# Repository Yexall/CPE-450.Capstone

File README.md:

# CPE-450.Capstone
Authors:
- Cameron Bracken
- Ryan Jacoby
- Noa Johnson
- Yexelle Nash Segovia

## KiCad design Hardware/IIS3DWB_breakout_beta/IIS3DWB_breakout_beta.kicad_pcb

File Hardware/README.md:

# Haas Hooligans Hardware

Board assembly prints and schematics for the final prototypes are provided in this directory. The three folders (IIS3DWB\_eval, IIS3DWB\_breakout\_beta, and hw\_alpha) have more detailed design sources for each of the PCBs designed.

## Main Board
Bringup notes and notes for the next revision of the main board can be found [here](https://github.com/Yexall/CPE-450.Capstone/blob/main/Hardware/hw_alpha/bringup_notes.md)

An interactive HTML BOM can be found [here](https://html-preview.github.io/?url=https://github.com/Yexall/CPE-450.Capstone/blob/main/Hardware/hw_alpha/bom/ibom.html)

A downloadable PDF assembly document can be found [here](https://github.com/Yexall/CPE-450.Capstone/blob/main/Hardware/hw_alpha/plots/hw_alpha__Assembly.pdf)

A downloadable PDF schematic can be found [here](https://github.com/Yexall/CPE-450.Capstone/blob/main/Hardware/hw_alpha/hw_alpha_schem.pdf)

## IIS3DWB Breakout
A downloadable PDF assembly document can be found [here](https://github.com/Yexall/CPE-450.Capstone/blob/main/Hardware/IIS3DWB_breakout_beta/plots/IIS3DWB_breakout_beta__Assembly.pdf)

A downloadable PDF schematic can be found [here](https://github.com/Yexall/CPE-450.Capstone/blob/main/Hardware/IIS3DWB_breakout_beta/IIS3DWB_breakout_beta_schem.pdf)

## Copyright
Copyright Ryan Jacoby, Cal Poly CPE Department, Cal Poly IME Department 2025.

This source describes Open Hardware and is licensed under the CERN-OHL-P v2

You may redistribute and modify this documentation and make products
using it under the terms of the CERN-OHL-P v2 (https:/cern.ch/cern-ohl).
This documentation is distributed WITHOUT ANY EXPRESS OR IMPLIED
WARRANTY, INCLUDING OF MERCHANTABILITY, SATISFACTORY QUALITY
AND FITNESS FOR A PARTICULAR PURPOSE. Please see the CERN-OHL-P v2
for applicable conditions

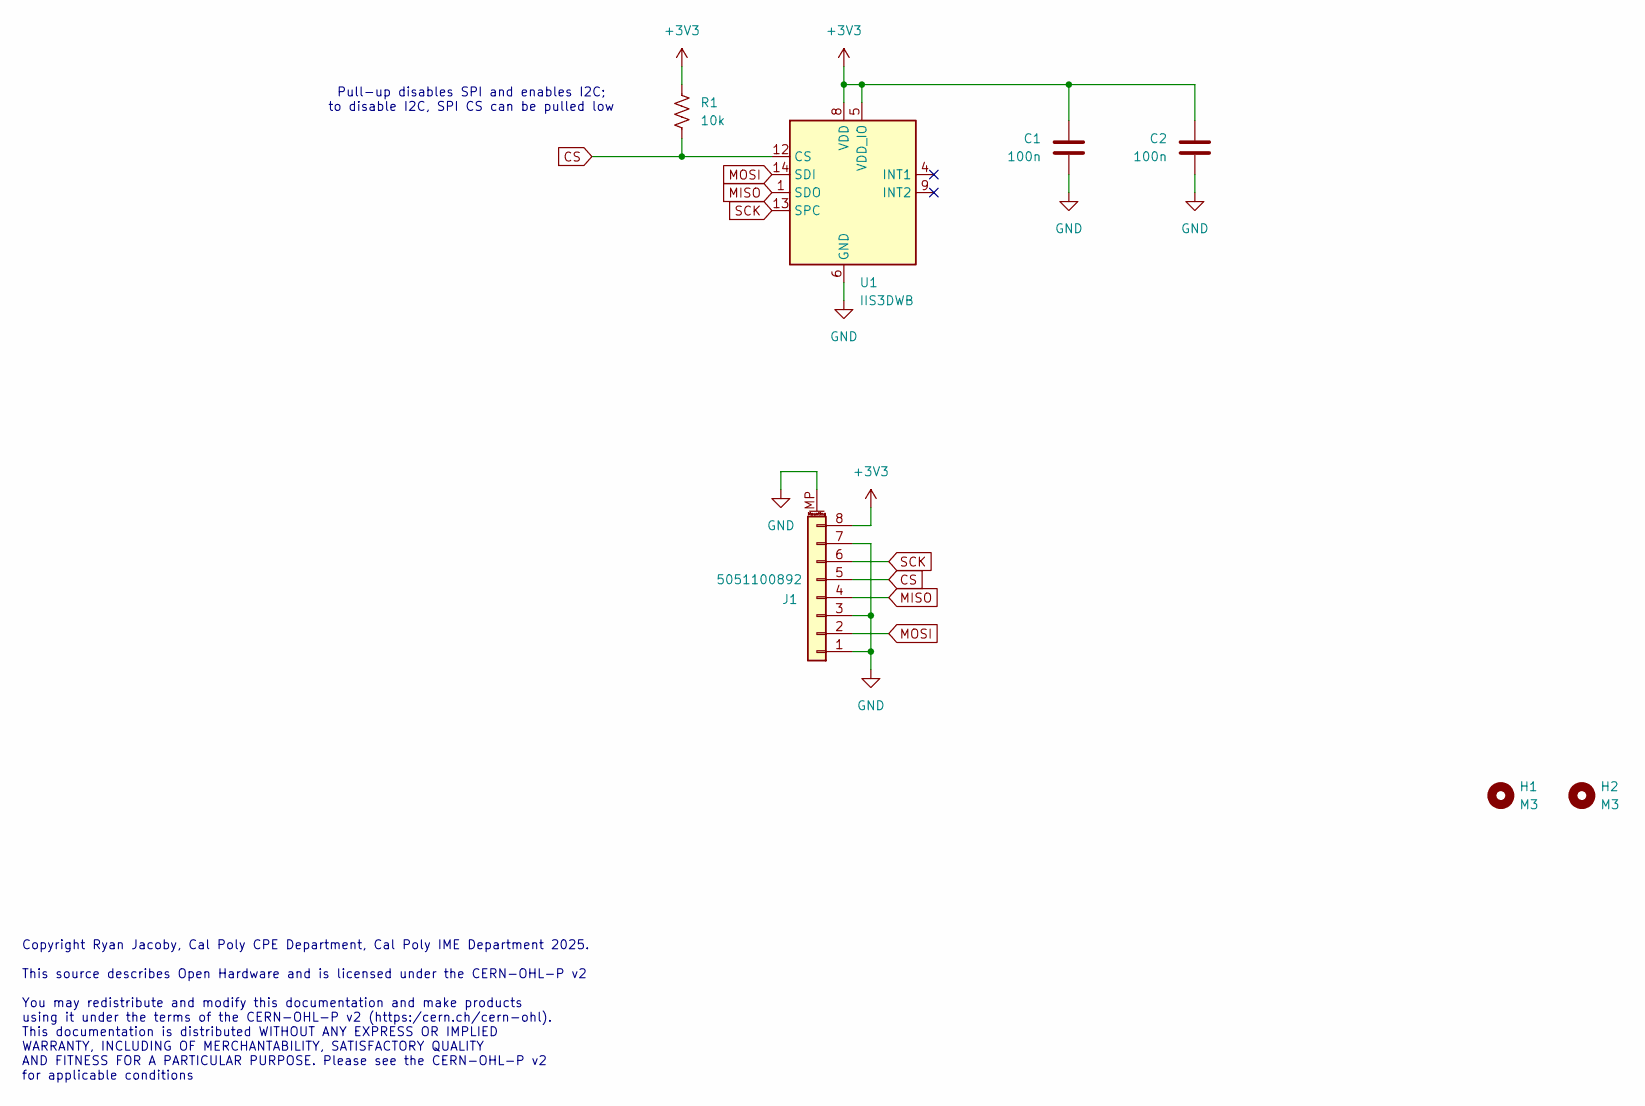
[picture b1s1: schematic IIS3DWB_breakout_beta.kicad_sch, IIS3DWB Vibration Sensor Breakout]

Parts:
C1, C2: 100n; C_0603_1608Metric
H1, H2: M3; MountingHole_3.2mm_M3
J1: 5051100892; CON_5051100892_MOL
R1: 10k; R_0603_1608Metric
U1: IIS3DWB; LGA-14_3x2.5mm_P0.5mm_LayoutBorder3x4y; MPN IIS3DWBTR

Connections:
+3V3: C1.1, C2.1, J1.8, R1.1, U1.5 (VDD_IO), U1.8 (VDD)
CS: J1.5, R1.2, U1.12 (CS)
GND: C1.2, C2.2, J1.1, J1.3, J1.7, J1.MP (MountPin), U1.2 (GND), U1.3 (GND), U1.6 (GND), U1.7 (GND)
MISO: J1.4, U1.1 (SDO)
MOSI: J1.2, U1.14 (SDI)
SCK: J1.6, U1.13 (SPC)

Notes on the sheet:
Copyright Ryan Jacoby, Cal Poly CPE Department, Cal Poly IME Department 2025. This source describes Open Hardware and is licensed under the CERN-OHL-P v2 You may redistribute and modify this documentation and make products using it under the terms of the CERN-OHL-P v2 (https:/cern.ch/cern-ohl). Thi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
Pull-up disables SPI and enables I2C; to disable I2C, SPI CS can be pulled low

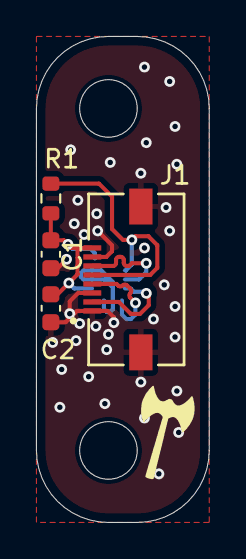
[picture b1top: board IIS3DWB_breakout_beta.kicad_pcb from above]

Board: 2 copper layers, 9.6 x 27.0 mm, 7 parts (1 on the bottom side), 6 nets.

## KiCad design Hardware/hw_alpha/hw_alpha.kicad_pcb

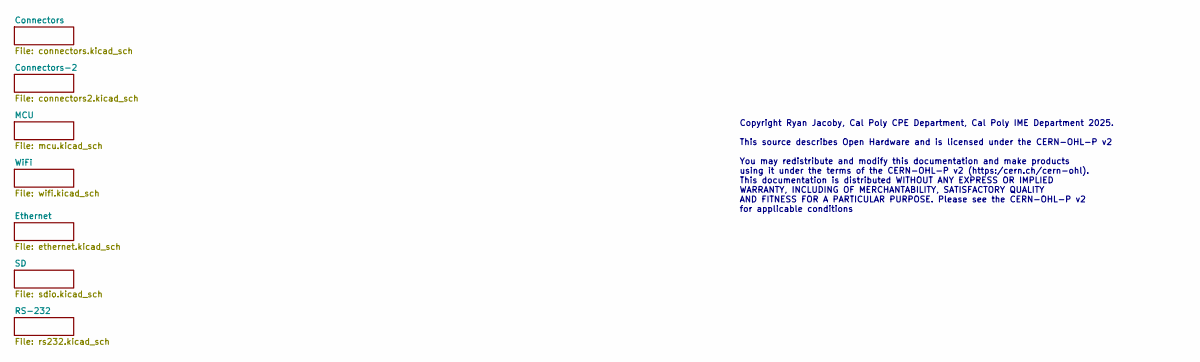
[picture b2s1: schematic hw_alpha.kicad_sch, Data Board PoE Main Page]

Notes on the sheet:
Copyright Ryan Jacoby, Cal Poly CPE Department, Cal Poly IME Department 2025. This source describes Open Hardware and is licensed under the CERN-OHL-P v2 You may redistribute and modify this documentation and make products using it under the terms of the CERN-OHL-P v2 (https:/cern.ch/cern-ohl). Thi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

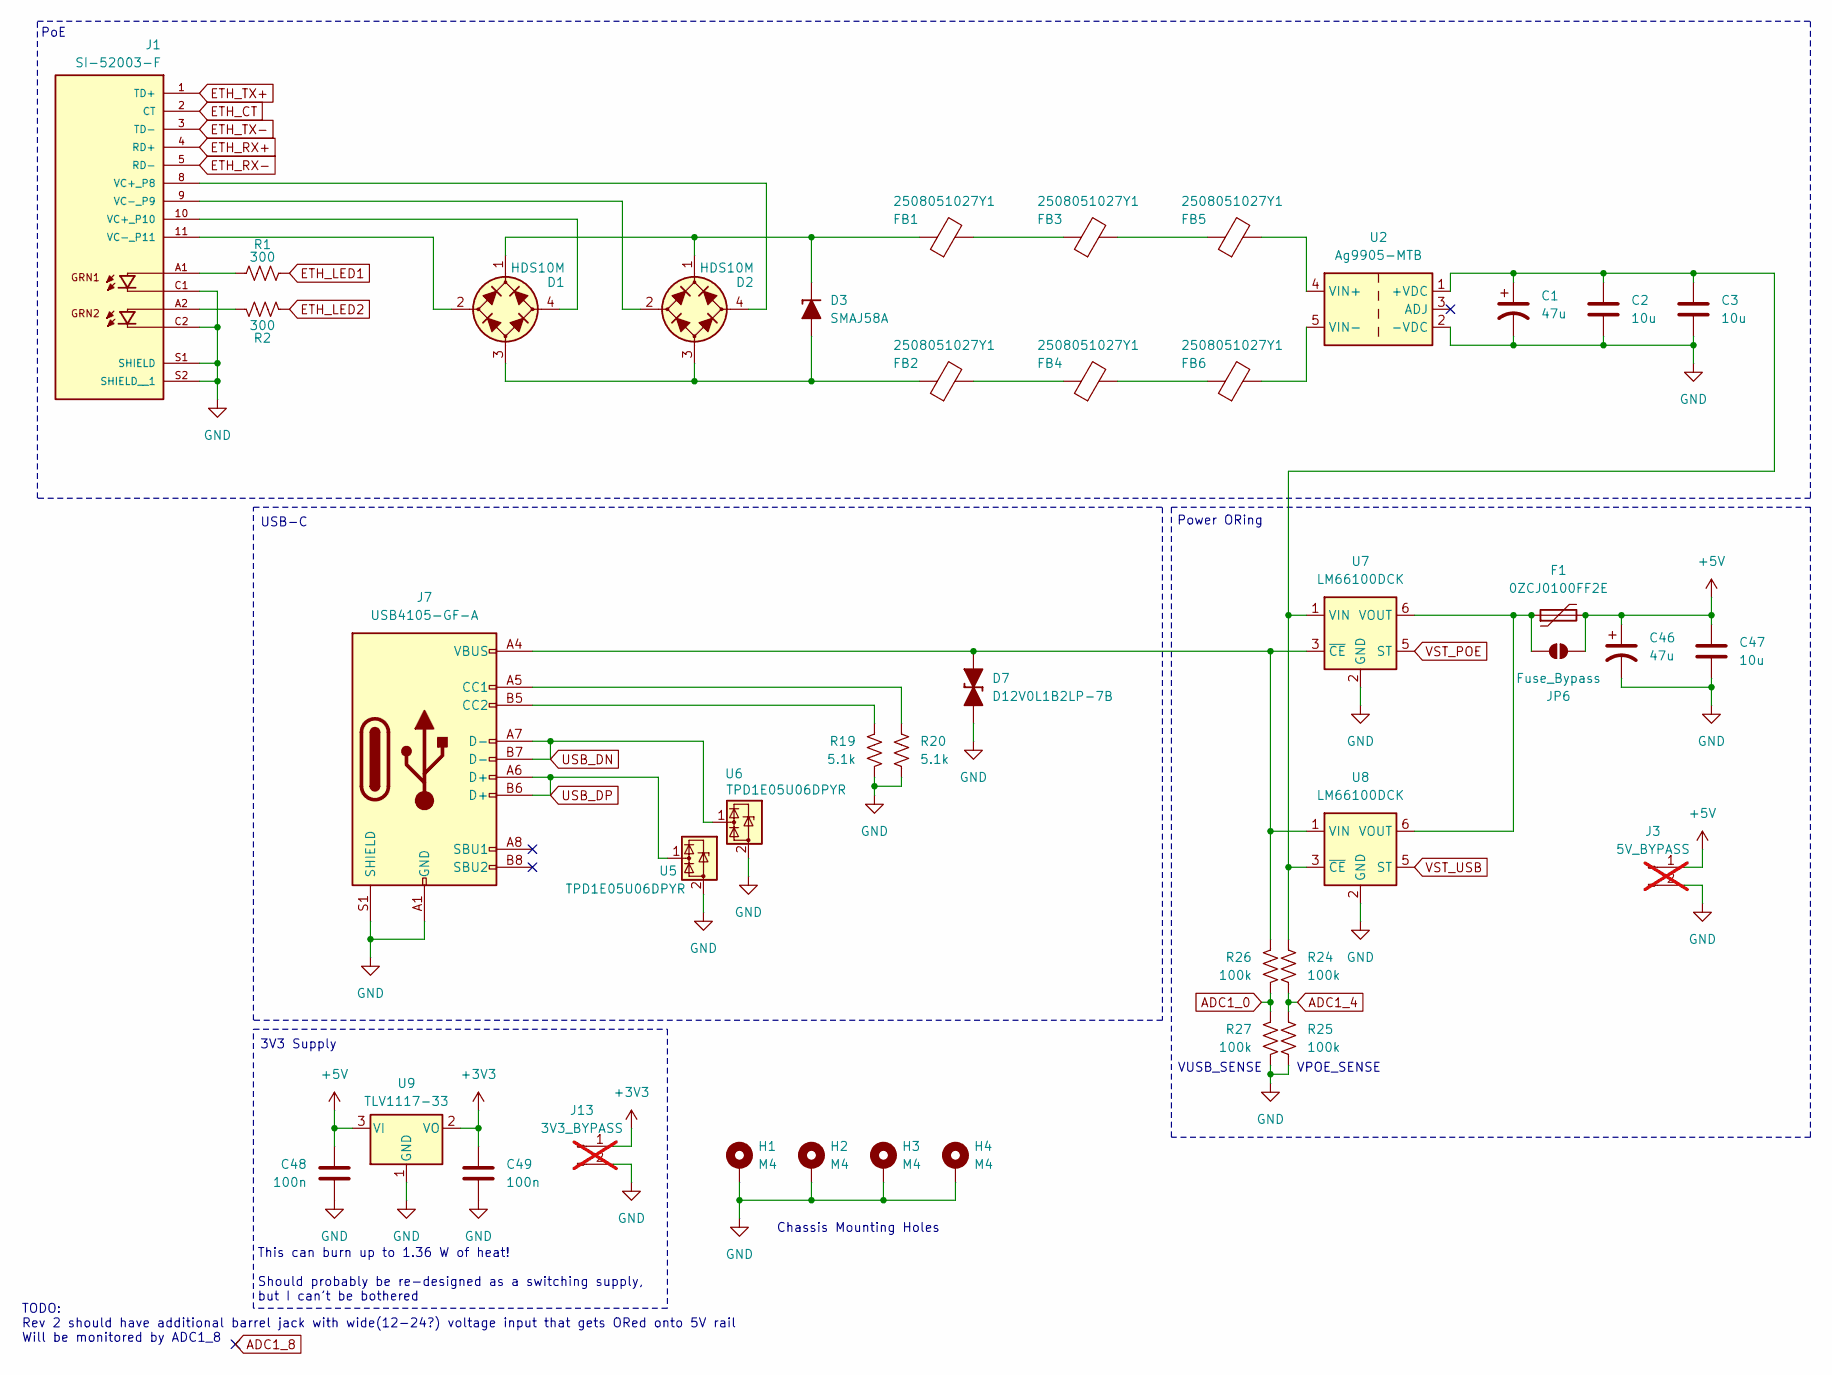
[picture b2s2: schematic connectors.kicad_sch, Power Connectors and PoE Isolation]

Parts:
C1, C46: 47u; CP_Elec_5x5.4
C2, C3, C47: 10u; C_0805_2012Metric
C48, C49: 100n; C_0603_1608Metric
D1, D2: HDS10M; HDS_DIO
D3: SMAJ58A; D_SMA
D7: D12V0L1B2LP-7B; D_0402_1005Metric
F1: 0ZCJ0100FF2E; Fuse_1206_3216Metric
FB1, FB2, FB3, FB4, FB5, FB6: 2508051027Y1; L_0805_2012Metric
H1, H2, H3, H4: M4; MountingHole_4.3mm_M4_Pad_Via
J1: SI-52003-F; BEL_SI-52003-F
J3: 5V_BYPASS; PinSocket_1x02_P2.54mm_Vertical; not fitted
J7: USB4105-GF-A; GCT_USB4105-GF-A
J13: 3V3_BYPASS; PinSocket_1x02_P2.54mm_Vertical; not fitted
JP6: Fuse_Bypass; SolderJumper-2_P1.3mm_Open_TrianglePad1.0x1.5mm
R1, R2: 300; R_0603_1608Metric
R19, R20: 5.1k; R_0603_1608Metric
R24, R25, R26, R27: 100k; R_0603_1608Metric
U2: Ag9905-MTB; Converter_DCDC_Silvertel_AG99xxMTB_Hand_Solder
U5, U6: TPD1E05U06DPYR; Texas_DPY0002A_0.6x1mm_P0.65mm
U7, U8: LM66100DCK; SOT-363_SC-70-6
U9: TLV1117-33; SOT-223-3_TabPin2

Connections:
+3V3: C49.1, J13.1, U9.2 (VO); also elsewhere on the board
+5V: C46.1, C47.1, C48.1, F1.2, J3.1, JP6.2 (B), U9.3 (VI); also elsewhere on the board
ADC1_0: R26.2, R27.1; also elsewhere on the board
ADC1_4: R24.2, R25.1; also elsewhere on the board
ETH_CT: J1.2 (CT); also elsewhere on the board
ETH_LED1: R1.2; also elsewhere on the board
ETH_LED2: R2.2; also elsewhere on the board
ETH_RX+: J1.4 (RD+); also elsewhere on the board
ETH_RX-: J1.5 (RD-); also elsewhere on the board
ETH_TX+: J1.1 (TD+); also elsewhere on the board
ETH_TX-: J1.3 (TD-); also elsewhere on the board
GND: C1.2, C2.2, C3.2, C46.2, C47.2, C48.2, C49.2, D7.1 (K), H1.1, H2.1, H3.1, H4.1, J1.C1, J1.C2, J1.S1 (SHIELD), J1.S2 (SHIELD__1), J3.2, J7.A1 (GND), J7.A12 (GND), J7.B1 (GND), J7.B12 (GND), J7.S1 (SHIELD), J13.2, R19.2, R20.2, R25.2, R27.2, U2.2 (-VDC), U5.2 (GND), U6.2 (GND), U7.2 (GND), U8.2 (GND), U9.1 (GND); also elsewhere on the board
unnamed: D1.2 (1), J1.11 (VC-_P11)
unnamed: D1.4 (2), J1.10 (VC+_P10)
unnamed: D1.1 (+), D2.1 (+), D3.1 (K), FB1.1
unnamed: D1.3 (-), D2.3 (-), D3.2 (A), FB2.1
unnamed: D2.2 (1), J1.9 (VC-_P9)
unnamed: D2.4 (2), J1.8 (VC+_P8)
unnamed: D7.2 (A), J7.A4 (VBUS), J7.A9 (VBUS), J7.B4 (VBUS), J7.B9 (VBUS), R26.1, U7.3 (~CE), U8.1 (VIN)
unnamed: FB1.2, FB3.1
unnamed: FB2.2, FB4.1
unnamed: FB3.2, FB5.1
unnamed: FB4.2, FB6.1
unnamed: J1.A1, R1.1
unnamed: J1.A2, R2.1
unnamed: J7.A5 (CC1), R20.1
unnamed: J7.B5 (CC2), R19.1
unnamed: F1.1, JP6.1 (A), U7.6 (VOUT), U8.6 (VOUT)
unnamed: C1.1, C2.1, C3.1, R24.1, U2.1 (+VDC), U7.1 (VIN), U8.3 (~CE)
unnamed: FB5.2, U2.4 (VIN+)
unnamed: FB6.2, U2.5 (VIN-)
USB_DN: J7.A7 (D-), J7.B7 (D-), U6.1 (I/O); also elsewhere on the board
USB_DP: J7.A6 (D+), J7.B6 (D+), U5.1 (I/O); also elsewhere on the board
VST_POE: U7.5 (ST); also elsewhere on the board
VST_USB: U8.5 (ST); also elsewhere on the board

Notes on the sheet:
PoE
USB-C
Chassis Mounting Holes
This can burn up to 1.36 W of heat! Should probably be re-designed as a switching supply, but I can't be bothered
VPOE_SENSE
Power ORing
VUSB_SENSE
TODO: Rev 2 should have additional barrel jack with wide(12-24?) voltage input that gets ORed onto 5V rail Will be monitored by ADC1_8
3V3 Supply

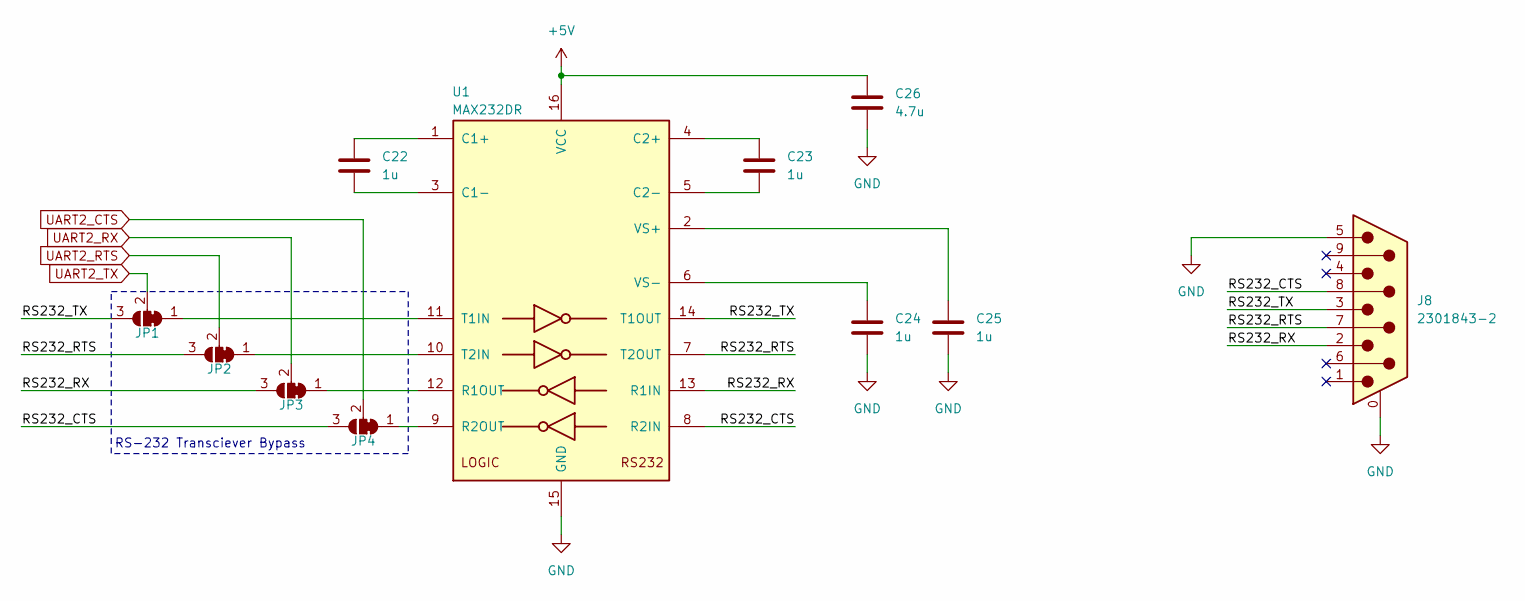
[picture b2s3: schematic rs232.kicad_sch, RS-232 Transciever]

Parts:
C22, C23, C24, C25: 1u; C_0603_1608Metric
C26: 4.7u; C_0603_1608Metric
J8: 2301843-2; DSUB-9_Pins_Horizontal_P2.77x2.84mm_EdgePinOffset9.90mm_Hou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
JP1, JP2, JP3, JP4: SolderJumper_3_Bridged12; SolderJumper-3_P1.3mm_Bridged12_RoundedPad1.0x1.5mm
U1: MAX232DR; SOIC-16_3.9x9.9mm_P1.27mm

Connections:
+5V: C26.1, U1.16 (VCC); also elsewhere on the board
/RS-232/RS232_CTS: J8.8, JP4.3 (B), U1.8 (R2IN)
/RS-232/RS232_RTS: J8.7, JP2.3 (B), U1.7 (T2OUT)
/RS-232/RS232_RX: J8.2, JP3.3 (B), U1.13 (R1IN)
/RS-232/RS232_TX: J8.3, JP1.3 (B), U1.14 (T1OUT)
GND: C24.2, C25.2, C26.2, J8.0 (PAD), J8.5, U1.15 (GND); also elsewhere on the board
unnamed: JP1.1 (A), U1.11 (T1IN)
unnamed: JP2.1 (A), U1.10 (T2IN)
unnamed: JP3.1 (A), U1.12 (R1OUT)
unnamed: JP4.1 (A), U1.9 (R2OUT)
unnamed: C22.1, U1.1 (C1+)
unnamed: C22.2, U1.3 (C1-)
unnamed: C23.1, U1.4 (C2+)
unnamed: C23.2, U1.5 (C2-)
unnamed: C25.1, U1.2 (VS+)
unnamed: C24.1, U1.6 (VS-)
UART2_CTS: JP4.2 (C); also elsewhere on the board
UART2_RTS: JP2.2 (C); also elsewhere on the board
UART2_RX: JP3.2 (C); also elsewhere on the board
UART2_TX: JP1.2 (C); also elsewhere on the board

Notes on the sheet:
RS-232 Transciever Bypass

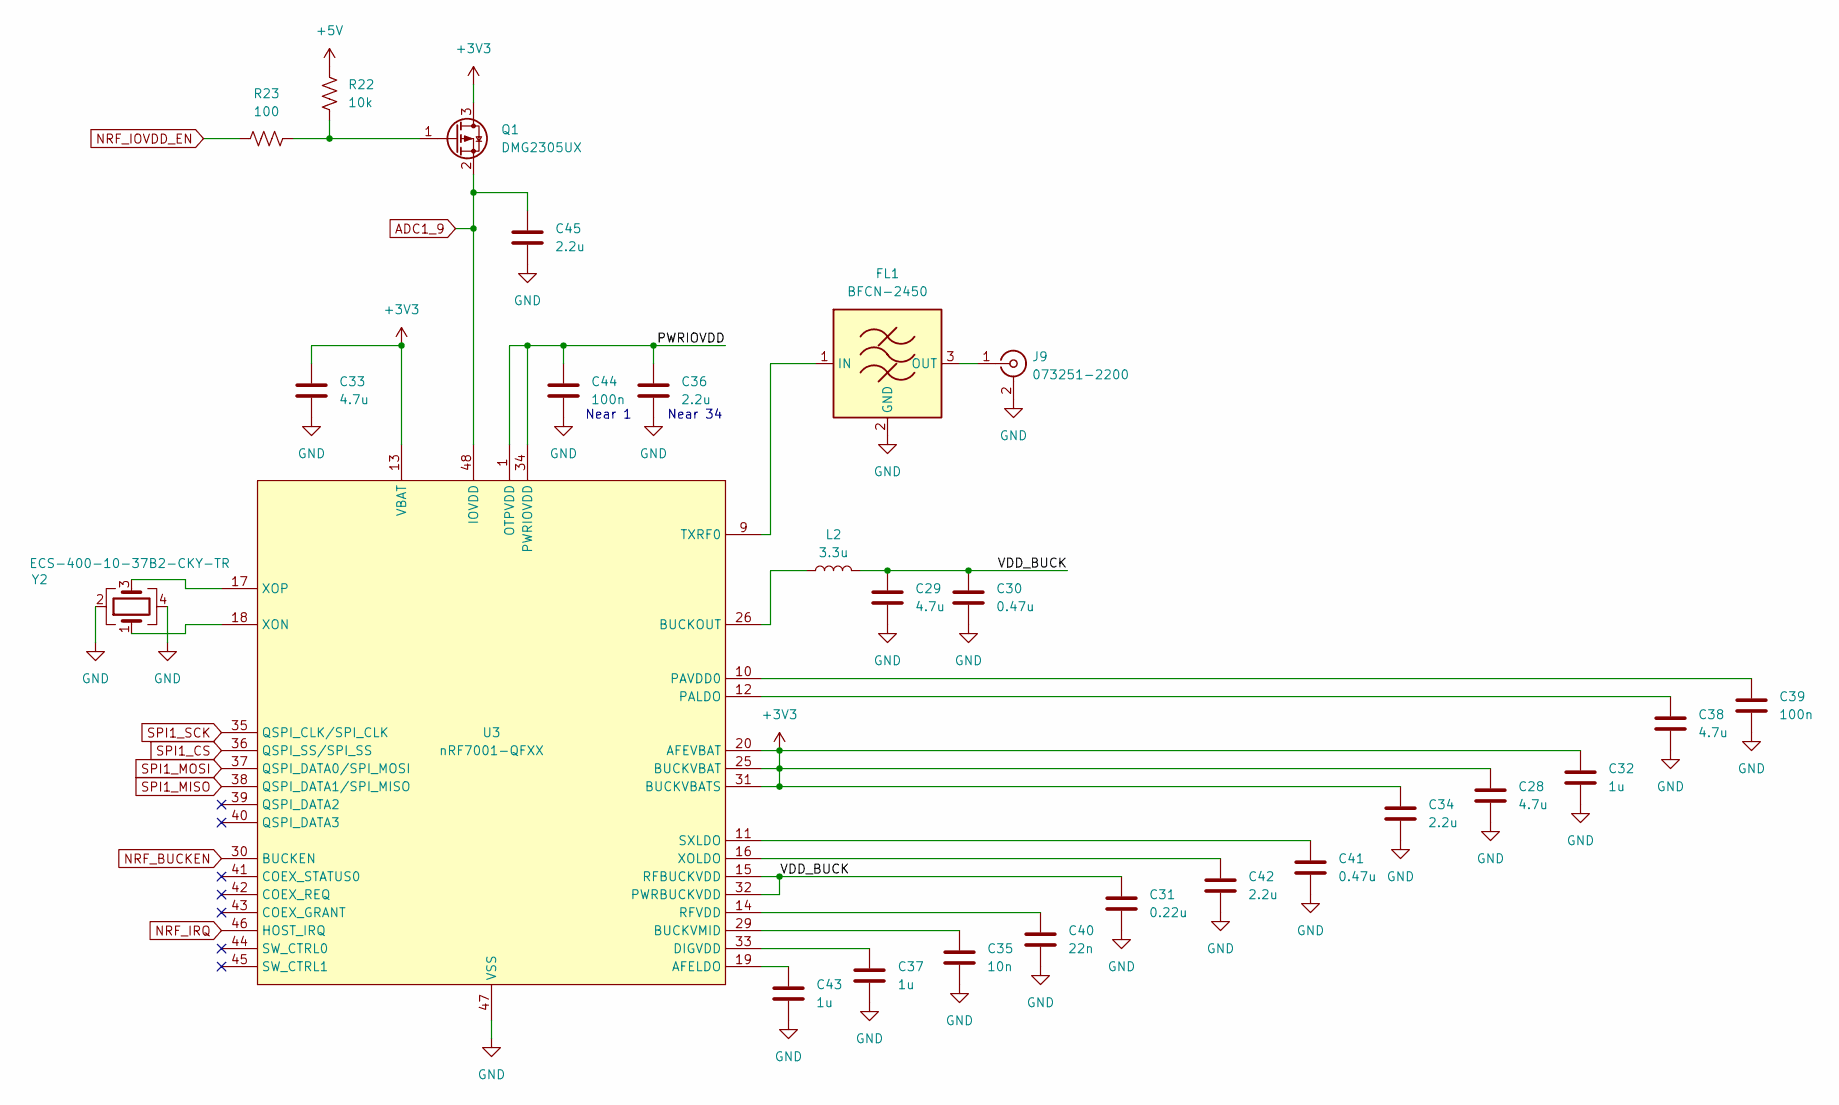
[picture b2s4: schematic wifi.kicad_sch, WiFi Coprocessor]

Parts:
C28, C29, C33, C38: 4.7u; C_0603_1608Metric
C30, C41: 0.47u; C_0603_1608Metric
C31: 0.22u; C_0402_1005Metric
C32, C37, C43: 1u; C_0603_1608Metric
C34, C36, C42, C45: 2.2u; C_0603_1608Metric
C35: 10n; C_0603_1608Metric
C39, C44: 100n; C_0603_1608Metric
C40: 22n; C_0603_1608Metric
FL1: BFCN-2450; Filter_Mini-Circuits_FV1206-4
J9: 073251-2200; SMA_Molex_73251-2200_Horizontal
L2: 3.3u; L_0805_2012Metric
Q1: DMG2305UX; SOT-23
R22: 10k; R_0603_1608Metric
R23: 100; R_0603_1608Metric
U3: nRF7001-QFXX; QFN-48-1EP_6x6mm_P0.4mm_EP4.6x4.6mm_ThermalVias
Y2: ECS-400-10-37B2-CKY-TR; Crystal_SMD_2016-4Pin_2.0x1.6mm

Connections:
+3V3: C28.1, C32.1, C33.1, C34.1, Q1.3 (D), U3.13 (VBAT), U3.20 (AFEVBAT), U3.25 (BUCKVBAT), U3.31 (BUCKVBATS); also elsewhere on the board
+5V: R22.1; also elsewhere on the board
/WiFi/PWRIOVDD: C36.1, C44.1, U3.1 (OTPVDD), U3.34 (PWRIOVDD)
/WiFi/VDD_BUCK: C29.1, C30.1, C31.1, L2.2, U3.15 (RFBUCKVDD), U3.32 (PWRBUCKVDD)
ADC1_9: C45.1, Q1.2 (S), U3.48 (IOVDD); also elsewhere on the board
GND: C28.2, C29.2, C30.2, C31.2, C32.2, C33.2, C34.2, C35.2, C36.2, C37.2, C38.2, C39.2, C40.2, C41.2, C42.2, C43.2, C44.2, C45.2, FL1.2 (GND), FL1.4 (GND), J9.2 (Ext), U3.8 (PAVDD1), U3.27 (BUCKVSS), U3.28 (BUCKVSS), U3.47 (VSS), U3.49 (EP), Y2.2, Y2.4; also elsewhere on the board
NRF_BUCKEN: U3.30 (BUCKEN); also elsewhere on the board
NRF_IOVDD_EN: R23.1; also elsewhere on the board
NRF_IRQ: U3.46 (HOST_IRQ); also elsewhere on the board
unnamed: FL1.1 (IN), U3.9 (TXRF0)
unnamed: FL1.3 (OUT), J9.1 (In)
unnamed: Q1.1 (G), R22.2, R23.2
unnamed: C43.1, U3.19 (AFELDO)
unnamed: L2.1, U3.26 (BUCKOUT)
unnamed: C35.1, U3.29 (BUCKVMID)
unnamed: C37.1, U3.33 (DIGVDD)
unnamed: C38.1, U3.12 (PALDO)
unnamed: C39.1, U3.10 (PAVDD0)
unnamed: C40.1, U3.14 (RFVDD)
unnamed: C41.1, U3.11 (SXLDO)
unnamed: C42.1, U3.16 (XOLDO)
unnamed: U3.18 (XON), Y2.1
unnamed: U3.17 (XOP), Y2.3
SPI1_CS: U3.36 (QSPI_SS/SPI_SS); also elsewhere on the board
SPI1_MISO: U3.38 (QSPI_DATA1/SPI_MISO); also elsewhere on the board
SPI1_MOSI: U3.37 (QSPI_DATA0/SPI_MOSI); also elsewhere on the board
SPI1_SCK: U3.35 (QSPI_CLK/SPI_CLK); also elsewhere on the board

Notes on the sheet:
Near 34
Near 1

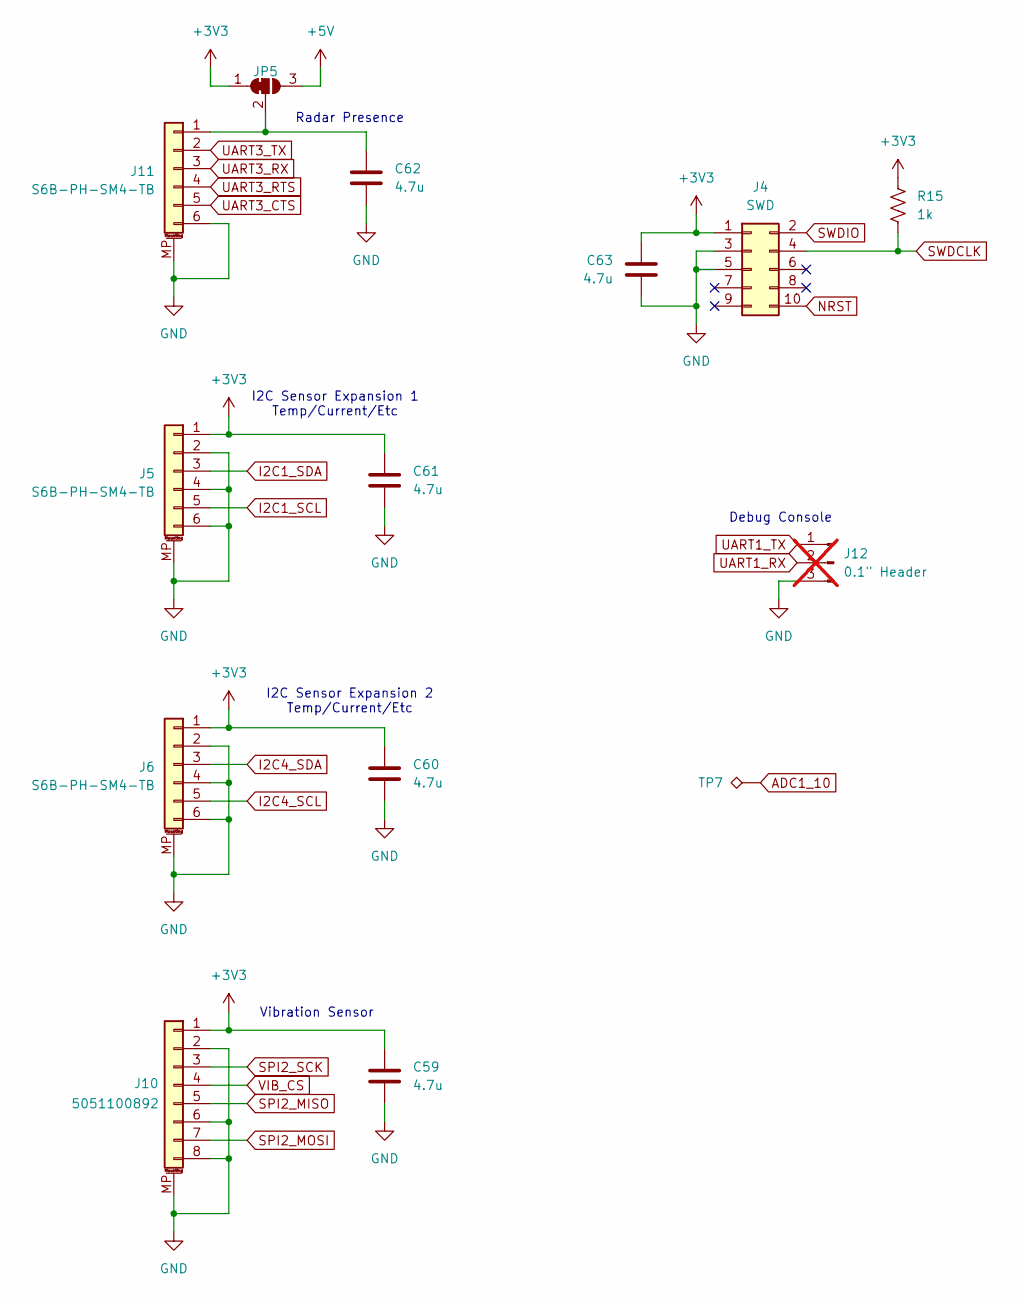
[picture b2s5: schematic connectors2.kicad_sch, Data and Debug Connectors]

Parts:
C59, C60, C61, C62, C63: 4.7u; C_0603_1608Metric
J4: SWD; CNC_3220-10-0300-00
J5, J6, J11: S6B-PH-SM4-TB; JST_PH_S6B-PH-SM4-TB_1x06-1MP_P2.00mm_Horizontal
J10: 5051100892; CON_5051100892_MOL
J12: 0.1" Header; PinHeader_1x03_P2.54mm_Vertical; not fitted
JP5: SolderJumper_3_Bridged12; SolderJumper-3_P1.3mm_Bridged12_RoundedPad1.0x1.5mm
R15: 1k; R_0603_1608Metric
TP7: TestPoint_Alt; TestPoint_Pad_2.0x2.0mm

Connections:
+3V3: C59.1, C60.1, C61.1, C63.1, J4.1, J5.1, J6.1, J10.1, JP5.1 (A), R15.1; also elsewhere on the board
+5V: JP5.3 (B); also elsewhere on the board
ADC1_10: TP7.1; also elsewhere on the board
GND: C59.2, C60.2, C61.2, C62.2, C63.2, J4.3, J4.5, J5.2, J5.4, J5.6, J5.MP (MountPin), J6.2, J6.4, J6.6, J6.MP (MountPin), J10.2, J10.6, J10.8, J10.MP (MountPin), J11.6, J11.MP (MountPin), J12.3; also elsewhere on the board
I2C1_SCL: J5.5; also elsewhere on the board
I2C1_SDA: J5.3; also elsewhere on the board
I2C4_SCL: J6.5; also elsewhere on the board
I2C4_SDA: J6.3; also elsewhere on the board
NRST: J4.10; also elsewhere on the board
unnamed: C62.1, J11.1, JP5.2 (C)
SPI2_MISO: J10.5; also elsewhere on the board
SPI2_MOSI: J10.7; also elsewhere on the board
SPI2_SCK: J10.3; also elsewhere on the board
SWDCLK: J4.4, R15.2; also elsewhere on the board
SWDIO: J4.2; also elsewhere on the board
UART1_RX: J12.2; also elsewhere on the board
UART1_TX: J12.1; also elsewhere on the board
UART3_CTS: J11.5; also elsewhere on the board
UART3_RTS: J11.4; also elsewhere on the board
UART3_RX: J11.3; also elsewhere on the board
UART3_TX: J11.2; also elsewhere on the board
VIB_CS: J10.4; also elsewhere on the board

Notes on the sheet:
Radar Presence
I2C Sensor Expansion 1 Temp/Current/Etc
Vibration Sensor
Debug Console
I2C Sensor Expansion 2 Temp/Current/Etc

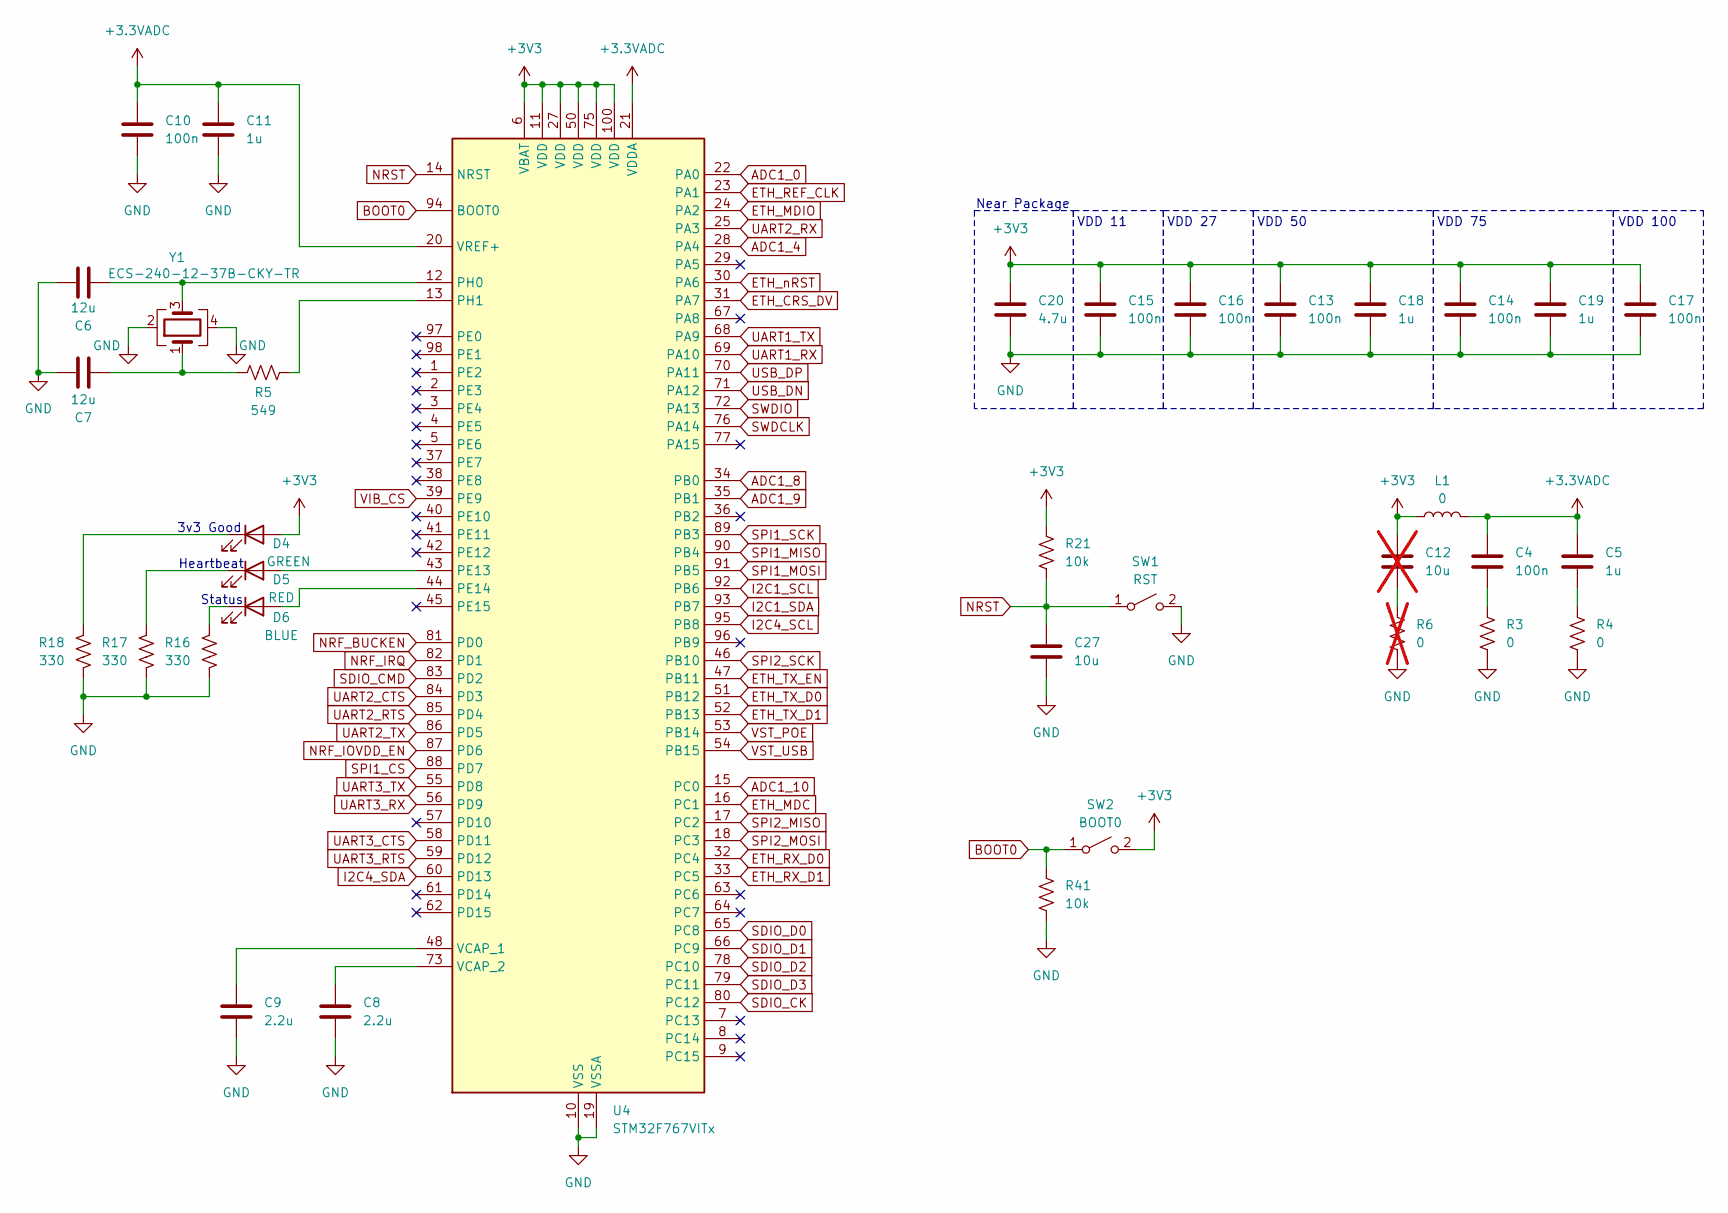
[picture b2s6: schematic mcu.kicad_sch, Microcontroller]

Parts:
C4, C10, C13, C14, C15, C16, C17: 100n; C_0603_1608Metric
C5, C11, C18, C19: 1u; C_0603_1608Metric
C6, C7: 12u; C_0805_2012Metric
C8, C9: 2.2u; C_0603_1608Metric
C12: 10u; C_0805_2012Metric; not fitted
C20: 4.7u; C_0603_1608Metric
C27: 10u; C_0805_2012Metric
D4: GREEN; LED_0603_1608Metric
D5: RED; LED_0603_1608Metric
D6: BLUE; LED_0603_1608Metric
L1: 0; R_0603_1608Metric
R3, R4: 0; R_0603_1608Metric
R5: 549; R_0603_1608Metric
R6: 0; R_0603_1608Metric; not fitted
R16, R17, R18: 330; R_0603_1608Metric
R21, R41: 10k; R_0603_1608Metric
SW1: RST; SolderJumper-2_P1.3mm_Open_RoundedPad1.0x1.5mm
SW2: BOOT0; SolderJumper-2_P1.3mm_Open_RoundedPad1.0x1.5mm
U4: STM32F767VITx; LQFP-100_14x14mm_P0.5mm
Y1: ECS-240-12-37B-CKY-TR; Crystal_SMD_2016-4Pin_2.0x1.6mm

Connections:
+3.3VADC: C4.1, C5.1, C10.1, C11.1, L1.2, U4.20 (VREF+), U4.21 (VDDA)
+3V3: C12.1, C13.1, C14.1, C15.1, C16.1, C17.1, C18.1, C19.1, C20.1, D4.2 (A), L1.1, R21.1, SW2.2 (B), U4.6 (VBAT), U4.11 (VDD), U4.27 (VDD), U4.50 (VDD), U4.75 (VDD), U4.100 (VDD); also elsewhere on the board
ADC1_0: U4.22 (PA0); also elsewhere on the board
ADC1_4: U4.28 (PA4); also elsewhere on the board
ADC1_8: U4.34 (PB0)
ADC1_9: U4.35 (PB1); also elsewhere on the board
ADC1_10: U4.15 (PC0); also elsewhere on the board
BOOT0: R41.1, SW2.1 (A), U4.94 (BOOT0)
ETH_CRS_DV: U4.31 (PA7); also elsewhere on the board
ETH_MDC: U4.16 (PC1); also elsewhere on the board
ETH_MDIO: U4.24 (PA2); also elsewhere on the board
ETH_REF_CLK: U4.23 (PA1); also elsewhere on the board
ETH_RX_D0: U4.32 (PC4); also elsewhere on the board
ETH_RX_D1: U4.33 (PC5); also elsewhere on the board
ETH_TX_D0: U4.51 (PB12); also elsewhere on the board
ETH_TX_D1: U4.52 (PB13); also elsewhere on the board
ETH_TX_EN: U4.47 (PB11); also elsewhere on the board
ETH_nRST: U4.30 (PA6); also elsewhere on the board
GND: C6.1, C7.1, C8.2, C9.2, C10.2, C11.2, C13.2, C14.2, C15.2, C16.2, C17.2, C18.2, C19.2, C20.2, C27.2, R3.2, R4.2, R6.2, R16.2, R17.2, R18.2, R41.2, SW1.2 (B), U4.10 (VSS), U4.19 (VSSA), U4.26 (VSS), U4.49 (VSS), U4.74 (VSS), U4.99 (VSS), Y1.2, Y1.4; also elsewhere on the board
I2C1_SCL: U4.92 (PB6); also elsewhere on the board
I2C1_SDA: U4.93 (PB7); also elsewhere on the board
I2C4_SCL: U4.95 (PB8); also elsewhere on the board
I2C4_SDA: U4.60 (PD13); also elsewhere on the board
NRF_BUCKEN: U4.81 (PD0); also elsewhere on the board
NRF_IOVDD_EN: U4.87 (PD6); also elsewhere on the board
NRF_IRQ: U4.82 (PD1); also elsewhere on the board
NRST: C27.1, R21.2, SW1.1 (A), U4.14 (NRST); also elsewhere on the board
unnamed: C4.2, R3.1
unnamed: C5.2, R4.1
unnamed: C7.2, R5.1, Y1.1
unnamed: C12.2, R6.1
unnamed: D4.1 (K), R18.1
unnamed: D5.2 (A), U4.43 (PE13)
unnamed: D5.1 (K), R17.1
unnamed: D6.2 (A), U4.44 (PE14)
unnamed: D6.1 (K), R16.1
unnamed: C6.2, U4.12 (PH0), Y1.3
unnamed: R5.2, U4.13 (PH1)
unnamed: C9.1, U4.48 (VCAP_1)
unnamed: C8.1, U4.73 (VCAP_2)
SDIO_CK: U4.80 (PC12); also elsewhere on the board
SDIO_CMD: U4.83 (PD2); also elsewhere on the board
SDIO_D0: U4.65 (PC8); also elsewhere on the board
SDIO_D1: U4.66 (PC9); also elsewhere on the board
SDIO_D2: U4.78 (PC10); also elsewhere on the board
SDIO_D3: U4.79 (PC11); also elsewhere on the board
SPI1_CS: U4.88 (PD7); also elsewhere on the board
SPI1_MISO: U4.90 (PB4); also elsewhere on the board
SPI1_MOSI: U4.91 (PB5); also elsewhere on the board
SPI1_SCK: U4.89 (PB3); also elsewhere on the board
SPI2_MISO: U4.17 (PC2); also elsewhere on the board
SPI2_MOSI: U4.18 (PC3); also elsewhere on the board
SPI2_SCK: U4.46 (PB10); also elsewhere on the board
SWDCLK: U4.76 (PA14); also elsewhere on the board
SWDIO: U4.72 (PA13); also elsewhere on the board
UART1_RX: U4.69 (PA10); also elsewhere on the board
UART1_TX: U4.68 (PA9); also elsewhere on the board
UART2_CTS: U4.84 (PD3); also elsewhere on the board
UART2_RTS: U4.85 (PD4); also elsewhere on the board
UART2_RX: U4.25 (PA3); also elsewhere on the board
UART2_TX: U4.86 (PD5); also elsewhere on the board
UART3_CTS: U4.58 (PD11); also elsewhere on the board
UART3_RTS: U4.59 (PD12); also elsewhere on the board
UART3_RX: U4.56 (PD9); also elsewhere on the board
UART3_TX: U4.55 (PD8); also elsewhere on the board
USB_DN: U4.71 (PA12); also elsewhere on the board
USB_DP: U4.70 (PA11); also elsewhere on the board
VIB_CS: U4.39 (PE9); also elsewhere on the board
VST_POE: U4.53 (PB14); also elsewhere on the board
VST_USB: U4.54 (PB15); also elsewhere on the board

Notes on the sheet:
Status
Heartbeat
VDD 11
VDD 100
VDD 27
VDD 50
3v3 Good
VDD 75
Near Package

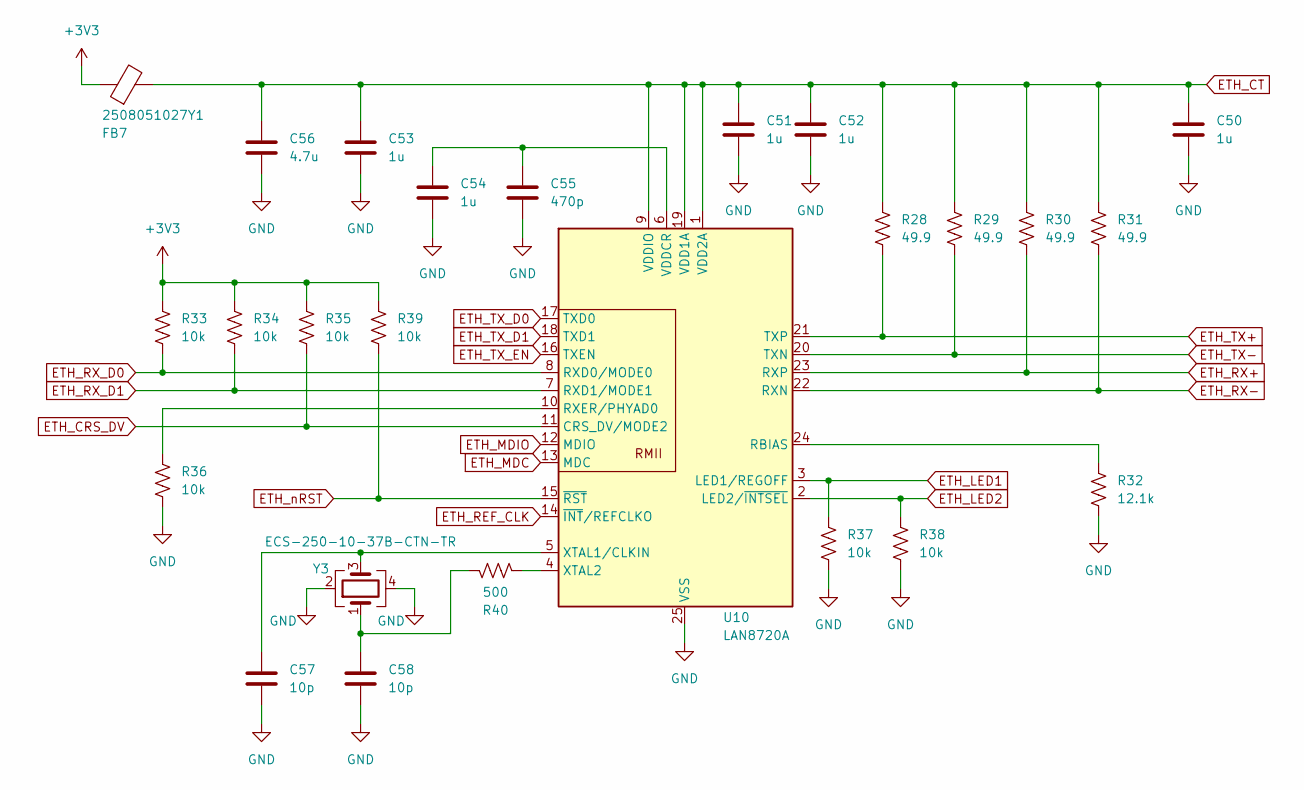
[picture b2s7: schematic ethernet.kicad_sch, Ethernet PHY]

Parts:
C50, C51, C52, C53, C54: 1u; C_0603_1608Metric
C55: 470p; C_0603_1608Metric
C56: 4.7u; C_0603_1608Metric
C57, C58: 10p; C_0402_1005Metric
FB7: 2508051027Y1; L_0805_2012Metric
R28, R29, R30, R31: 49.9; R_0603_1608Metric
R32: 12.1k; R_0603_1608Metric
R33, R34, R35, R36, R37, R38, R39: 10k; R_0603_1608Metric
R40: 500; R_0603_1608Metric
U10: LAN8720A; VQFN-24-1EP_4x4mm_P0.5mm_EP2.5x2.5mm_ThermalVias
Y3: ECS-250-10-37B-CTN-TR; Crystal_SMD_2016-4Pin_2.0x1.6mm

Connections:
+3V3: FB7.1, R33.1, R34.1, R35.1, R39.1; also elsewhere on the board
ETH_CRS_DV: R35.2, U10.11 (CRS_DV/MODE2); also elsewhere on the board
ETH_CT: C50.1, C51.1, C52.1, C53.1, C56.1, FB7.2, R28.1, R29.1, R30.1, R31.1, U10.1 (VDD2A), U10.9 (VDDIO), U10.19 (VDD1A); also elsewhere on the board
ETH_LED1: R37.1, U10.3 (LED1/REGOFF); also elsewhere on the board
ETH_LED2: R38.1, U10.2 (LED2/~INTSEL); also elsewhere on the board
ETH_MDC: U10.13 (MDC); also elsewhere on the board
ETH_MDIO: U10.12 (MDIO); also elsewhere on the board
ETH_REF_CLK: U10.14 (~INT/REFCLKO); also elsewhere on the board
ETH_RX+: R30.2, U10.23 (RXP); also elsewhere on the board
ETH_RX-: R31.2, U10.22 (RXN); also elsewhere on the board
ETH_RX_D0: R33.2, U10.8 (RXD0/MODE0); also elsewhere on the board
ETH_RX_D1: R34.2, U10.7 (RXD1/MODE1); also elsewhere on the board
ETH_TX+: R28.2, U10.21 (TXP); also elsewhere on the board
ETH_TX-: R29.2, U10.20 (TXN); also elsewhere on the board
ETH_TX_D0: U10.17 (TXD0); also elsewhere on the board
ETH_TX_D1: U10.18 (TXD1); also elsewhere on the board
ETH_TX_EN: U10.16 (TXEN); also elsewhere on the board
ETH_nRST: R39.2, U10.15 (~RST); also elsewhere on the board
GND: C50.2, C51.2, C52.2, C53.2, C54.2, C55.2, C56.2, C57.2, C58.2, R32.2, R36.2, R37.2, R38.2, U10.25 (VSS), Y3.2, Y3.4; also elsewhere on the board
unnamed: C58.1, R40.1, Y3.1
unnamed: R32.1, U10.24 (RBIAS)
unnamed: R36.1, U10.10 (RXER/PHYAD0)
unnamed: C54.1, C55.1, U10.6 (VDDCR)
unnamed: C57.1, U10.5 (XTAL1/CLKIN), Y3.3
unnamed: R40.2, U10.4 (XTAL2)
